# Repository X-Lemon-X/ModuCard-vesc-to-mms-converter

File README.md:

# VESC MMS converter

Mini version of MMS converter board for FVESC drivers.
Adds USB,CAN1,CAN2 and 12V, VCC line connection over Ethernet and XT60 cables and connects them to the driver.

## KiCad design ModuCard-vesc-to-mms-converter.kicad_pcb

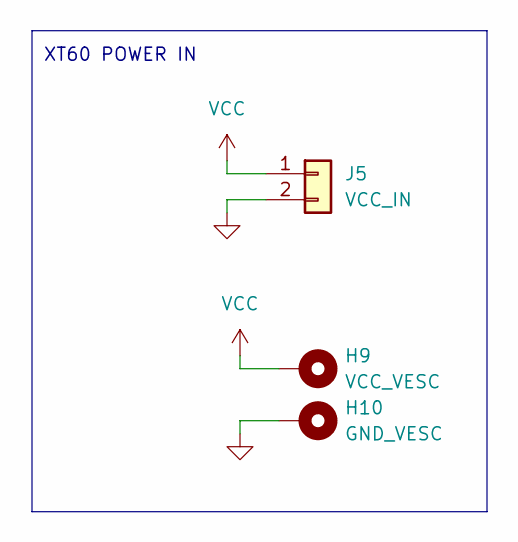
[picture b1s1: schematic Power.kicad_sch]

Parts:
H9: VCC_VESC; MountingHole_4mm_Pad_Via
H10: GND_VESC; MountingHole_4mm_Pad_Via
J5: VCC_IN; XT60-RightAngle-Adapter

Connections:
GND: H10.1, J5.2; also elsewhere on the board
VCC: H9.1, J5.1

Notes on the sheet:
XT60 POWER IN

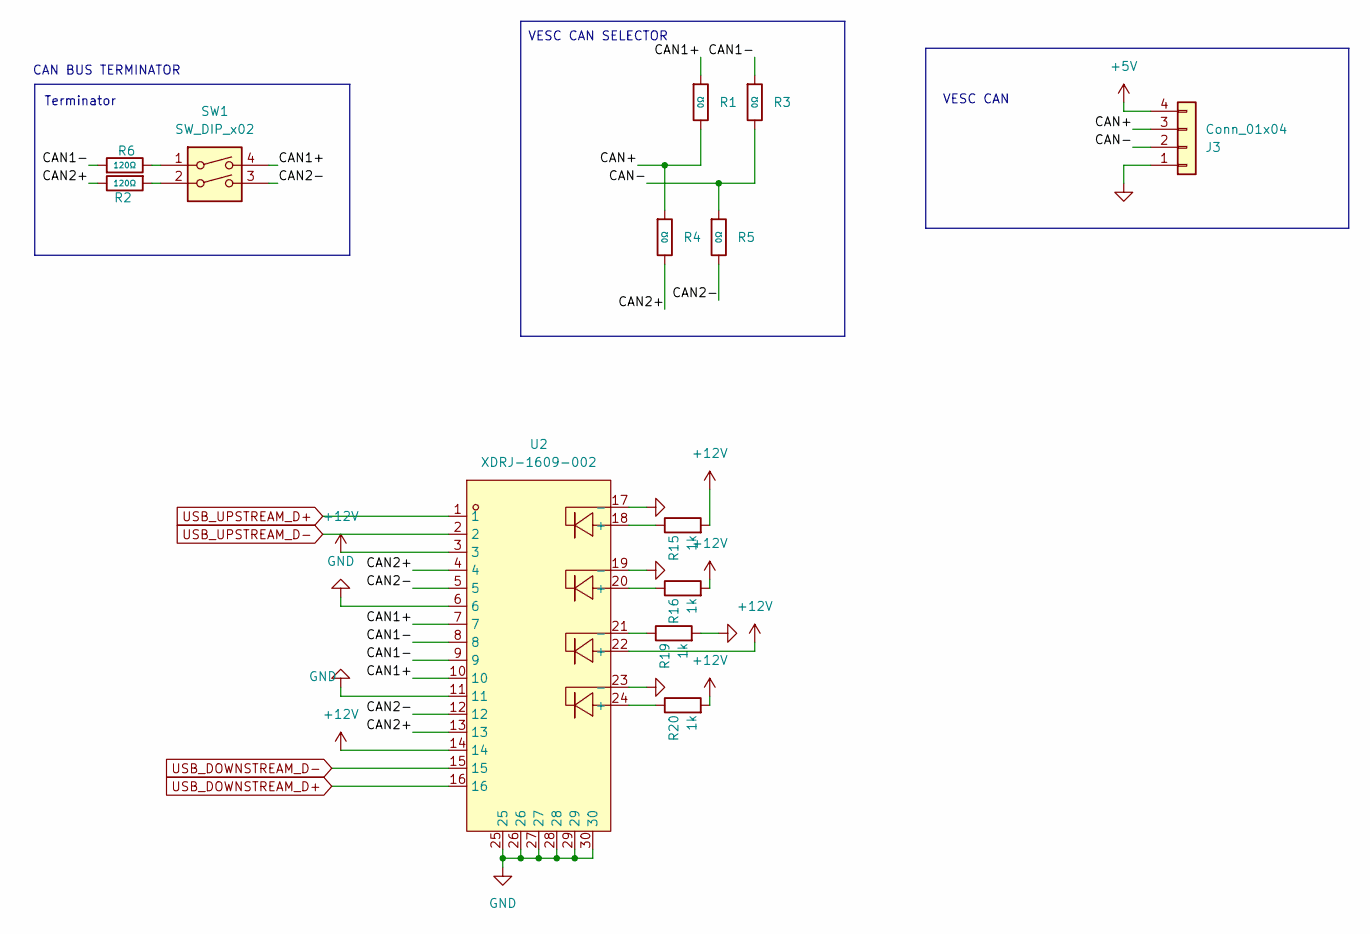
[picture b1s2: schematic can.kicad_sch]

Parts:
J3: Conn_01x04; JST_XH_B4B-XH-A_1x04_P2.50mm_Vertical
R1, R3, R4, R5: 0Ω; R_0603; Overload Voltage (Max) 75V; Tolerance ±1%; Part 0603WAF0000T5E; LCSC C21189
R2, R6: 120Ω; R_0603; Overload Voltage (Max) 75V; Tolerance ±1%; Part 0603WAF1200T5E; LCSC C22787
R15, R16, R19, R20: 1k; R_0402_1005Metric
SW1: SW_DIP_x02; SW_DIP_SPSTx02_Slide_6.7x6.64mm_W7.62mm_P2.54mm_LowProfile
U2: XDRJ-1609-002; RJ45-TH_XDRJ-1609-002; LCSC Part C7498193

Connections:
+5V: J3.4; also elsewhere on the board
+12V: R15.2, R16.2, R20.2, U2.3, U2.14, U2.22 (+)
/CAN/CAN1+: R1.1, SW1.4, U2.7, U2.10
/CAN/CAN1-: R3.1, R6.1, U2.8, U2.9
/CAN/CAN2+: R2.2, R4.2, U2.4, U2.13
/CAN/CAN2-: R5.2, SW1.3, U2.5, U2.12
/CAN/CAN+: J3.3, R1.2, R4.1
/CAN/CAN-: J3.2, R3.2, R5.1
GND: J3.1, R19.2, U2.6, U2.11, U2.17 (-), U2.19 (-), U2.23 (-), U2.25, U2.26, U2.27, U2.28, U2.29, U2.30; also elsewhere on the board
unnamed: R2.1, SW1.2
unnamed: R6.2, SW1.1
unnamed: R15.1, U2.18 (+)
unnamed: R16.1, U2.20 (+)
unnamed: R19.1, U2.21 (-)
unnamed: R20.1, U2.24 (+)
USB_DOWNSTREAM_D+: U2.16; also elsewhere on the board
USB_DOWNSTREAM_D-: U2.15; also elsewhere on the board
USB_UPSTREAM_D+: U2.1; also elsewhere on the board
USB_UPSTREAM_D-: U2.2; also elsewhere on the board

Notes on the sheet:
CAN BUS TERMINATOR
VESC CAN
Terminator
VESC CAN SELECTOR

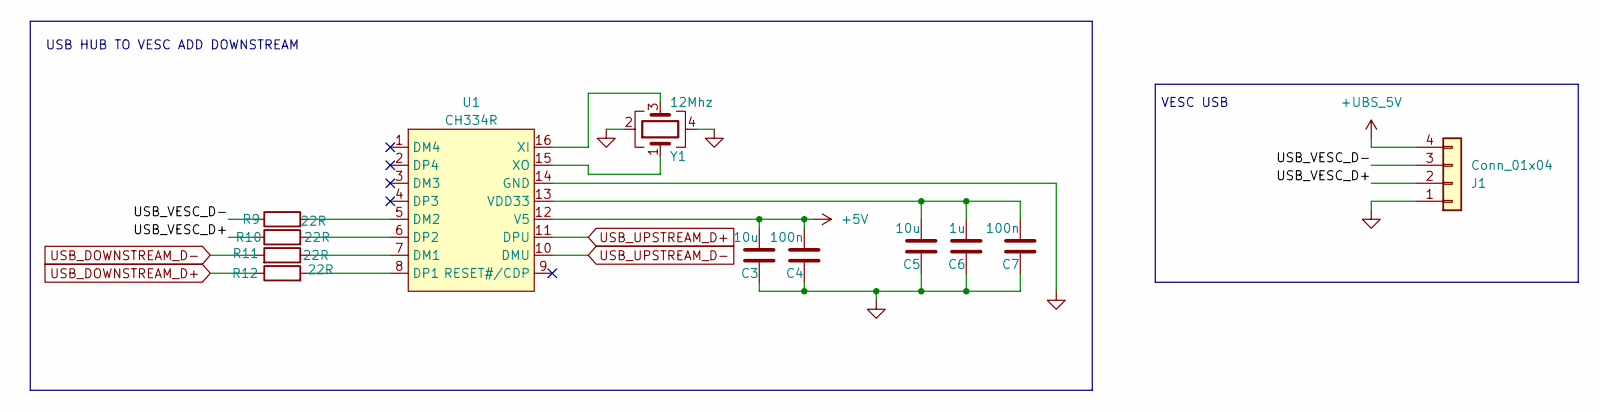
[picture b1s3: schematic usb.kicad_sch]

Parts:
C3, C5: 10u; C_0603_1608Metric
C4, C7: 100n; C_0402_1005Metric
C6: 1u; C_0603_1608Metric
J1: Conn_01x04; JST_XH_B4B-XH-A_1x04_P2.50mm_Vertical
R9, R10, R11, R12: 22R; R_0402_1005Metric
U1: CH334R; QSOP-16_3.9x4.9mm_P0.635mm
Y1: 12Mhz; Crystal_SMD_3225-4Pin_3.2x2.5mm

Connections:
+5V: C3.2, C4.2, U1.12 (V5); also elsewhere on the board
+UBS_5V: J1.4
/USB/USB_VESC_D+: J1.2, R10.1
/USB/USB_VESC_D-: J1.3, R9.1
GND: C3.1, C4.1, C5.1, C6.1, C7.1, J1.1, U1.14 (GND), Y1.2, Y1.4; also elsewhere on the board
unnamed: R11.1, U1.7 (DM1)
unnamed: R9.2, U1.5 (DM2)
unnamed: R12.2, U1.8 (DP1)
unnamed: R10.2, U1.6 (DP2)
unnamed: C5.2, C6.2, C7.2, U1.13 (VDD33)
unnamed: U1.16 (XI), Y1.3
unnamed: U1.15 (XO), Y1.1
USB_DOWNSTREAM_D+: R12.1; also elsewhere on the board
USB_DOWNSTREAM_D-: R11.2; also elsewhere on the board
USB_UPSTREAM_D+: U1.11 (DPU); also elsewhere on the board
USB_UPSTREAM_D-: U1.10 (DMU); also elsewhere on the board

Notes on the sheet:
USB HUB TO VESC ADD DOWNSTREAM
VESC USB

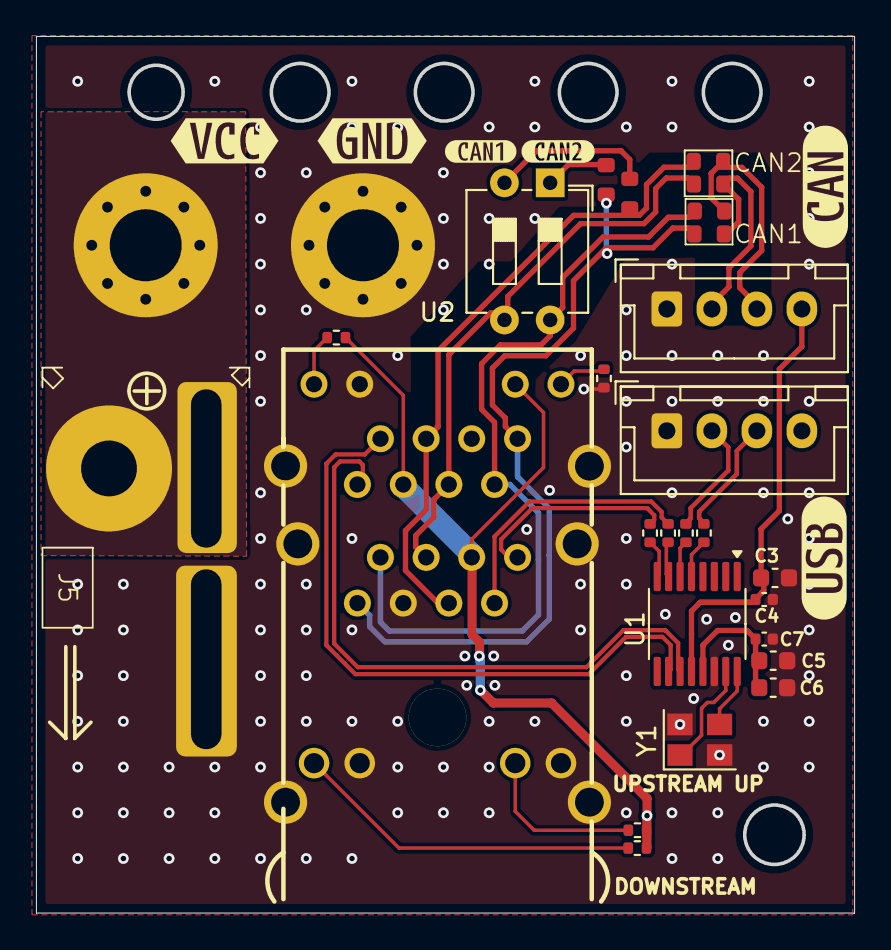
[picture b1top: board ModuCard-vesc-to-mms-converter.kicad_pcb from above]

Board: 2 copper layers, 45.3 x 48.6 mm, 34 parts (0 on the bottom side), 29 nets.

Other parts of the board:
kibuzzard-68DAF86F: G***; kibuzzard-68DAF86F
kibuzzard-68DAF865: G***; kibuzzard-68DAF865
kibuzzard-68DB0050: G***; kibuzzard-68DB0050
kibuzzard-674E4620: G***; kibuzzard-674E4620
kibuzzard-675D9C7D: G***; kibuzzard-675D9C7D
kibuzzard-675D9C73: G***; kibuzzard-675D9C73

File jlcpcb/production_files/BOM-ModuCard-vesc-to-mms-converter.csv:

Comment,Designator,Footprint,LCSC,Quantity
0Ω,"R1,R3,R4,R5",R_0603,C21189,4
120Ω,"R2,R6",R_0603,C22787,2
XDRJ-1609-002,U2,RJ45-TH_XDRJ-1609-002,C7498193,1
CH334R,U1,QSOP-16_3.9x4.9mm_P0.635mm,,1
10u,C5,C_0603_1608Metric,,1
SW_DIP_x02,SW1,SW_DIP_SPSTx02_Slide_6.7x6.64mm_W7.62mm_P2.54mm_LowProfile,,1
22R,R11,R_0402_1005Metric,,1
22R,R12,R_0402_1005Metric,,1
VCC_IN,J5,XT60-RightAngle-Adapter,,1
12Mhz,Y1,Crystal_SMD_3225-4Pin_3.2x2.5mm,,1
22R,R9,R_0402_1005Metric,,1
1u,C6,C_0603_1608Metric,,1
10u,C3,C_0603_1608Metric,,1
100n,C4,C_0402_1005Metric,,1
100n,C7,C_0402_1005Metric,,1
22R,R10,R_0402_1005Metric,,1
Conn_01x04,J1,JST_XH_B4B-XH-A_1x04_P2.50mm_Vertical,,1
Conn_01x04,J3,JST_XH_B4B-XH-A_1x04_P2.50mm_Vertical,,1
1k,R20,R_0402_1005Metric,,1
1k,R19,R_0402_1005Metric,,1
1k,R16,R_0402_1005Metric,,1
1k,R15,R_0402_1005Metric,,1

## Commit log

2025-09-29 rev v3 tiny
2025-09-30 rev 1
2025-11-06 fix chinczyk funckup
